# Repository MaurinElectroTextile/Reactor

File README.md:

# Tricot Reactor

### Musicals clothing made out of stretch knitted fabric sensor

S’habiller avec des vêtements technologiques c’est stylé! c’est un jeu comme le cosplay, une manière d’incarner son temps dans la mixité des influences passées, présentes et futures. Les vêtements interactifs et musicaux que nous imaginons pourraient s’inscrire dans une démarche artistique et performative mais nous avons décidé de nous adresser à un public plus large. Augmenté d'un "parfum sonore" le tricot Reacor est une sorte de vetement instrument. Rendu réactif grâce à l’intégration d’une petite carte électronique, le tricot Reactor permet d’imaginer une multitude de modèles de vêtements instruments. Tricoté à la main à partir de fils de laine et de fils conducteurs, la maille permet ainsi de capter l’élongation, la tension du tissu ainsi que les plis et contacts de la matière pour déclencher ou contrôler des sons. Une attention particulière est portée à l’intégration de l'électronique qui disparaît totalement au profit d’une esthétique simple. Intergénérationnel, ce projet est aussi un prétexte pour organiser des ateliers avec des grand mères branchées qui pourront remettre leur tricot au goût du jour.

## Scénarios

### Suivi de partition
A chaque fois que l’on bouge, presse ou plie le tricot, on "avance" d’une note dans une mélodie. Le rythme de cette mélodie correspond ainsi au rythme du mouvement de celui ou celle qui porte le vêtement et la composition fonctionne en boucle.

### Aléatoire contrôlé
Nous choisissons ici de distinguer plusieurs typologies de mouvement calme, en marche, excité, etc. Chacune de ces typologies est déterminée par la fréquence des mouvements captés. Plus on s’excite, plus les sons déclenchés sont aigus et distordus, à l’inverse, plus on est calme et plus les sons se réduisent à une sonorité simple.

### Le son extensible
Le stress exercé sur le tricot est générateur d’un son qui varie en relation directe avec l’étirement de la matière, plus le tricot est tendu plus le son est aigu. L’onde sonore est générée par synthèse. Une carte électronique dédiée permet de programmer plusieurs types de sons qui se rapprochent des sons 8-bit. Cette orientation fera l’objet d’une mise au point ultérieure car vous avons souhaité privilégier dans un premier temps une solution qui utilise des samples.

### Le son polyphonique
Dans ce dernier scénario le son sera généré par un téléphone portable assisté d’un mini système son. Ce téléphone sera aussi équipé d’une application musicale contrôlée par le vêtement. Pour réaliser un premier prototype nous avons choisi de travailler avec le système Android et donc d’aborder le développement d’une application en Java...

## Electronic
Pull on the knit cause resistor drop down. A voltage divider circuit is used to convert resistor variation into voltage value (Vs). This is done by adding a single 10K resistor (R2). To reduce power consumption of the voltage divider, the circuit is supplied (VCC) with a digital IO pin that allow on/off switching.The sketch is also implementing sleep mode.

The first prototype was using an ATTiny85 and a SOMO-4D (embedded audio-sound module) to build a small stand alone audio player. [This tutoriel explain how to program ATTiny with Arduino](http://hlt.media.mit.edu/?p=1229)

## TODO
- Translate the text in english
- Replace the SOMO with the [Teensy 3.2](https://www.pjrc.com/teensy/teensy31.html)
- Add a small amplifier

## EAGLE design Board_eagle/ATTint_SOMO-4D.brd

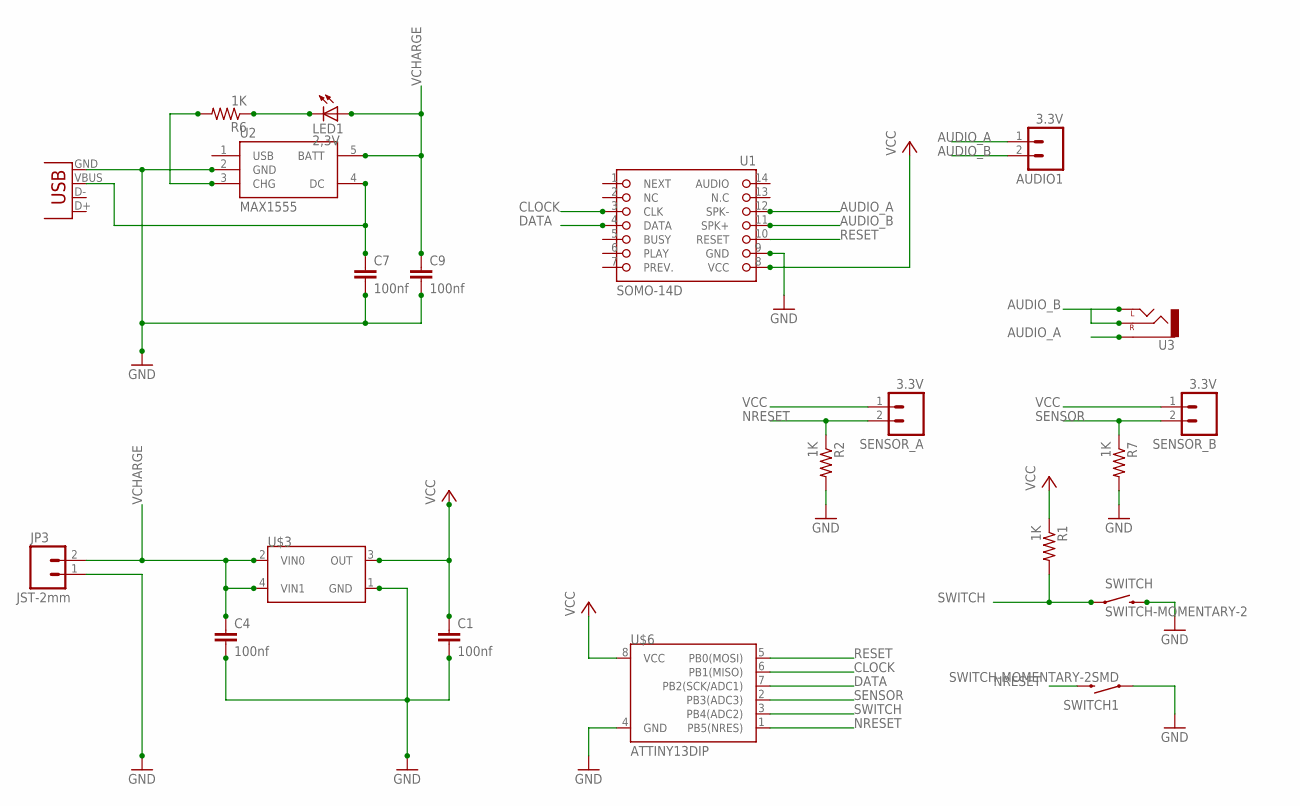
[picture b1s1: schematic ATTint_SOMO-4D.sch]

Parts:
AUDIO1: 3.3V; 1X02_LOCK_LONGPADS
C1, C4, C7, C9: 100nf; 0805
JP3: JST-2mm; JST-2-SMD
LED1: 2,3V; CHIP-LED0805
R1, R2, R6, R7: 1K; 0805
SENSOR_A: 3.3V; 1X02_LOCK_LONGPADS
SENSOR_B: 3.3V; 1X02_LOCK_LONGPADS
SWITCH: SWITCH-MOMENTARY-2; TACTILE_SWITCH_TALL
SWITCH1: SWITCH-MOMENTARY-2SMD; TACTILE_SWITCH_SMD
U1: SOMO-14D
U2: MAX1555; SOT23-5
U3: AUDIO-JACKSMD2; AUDIO-JACK-3.5MM-SMD
U$3: MCP1703; SOT-89
U$6: ATTINY13DIP; DIP08
X3: USB-SMD-NS; USB-MINIB-NOSTOP

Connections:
AUDIO_A: AUDIO1.1, U1.12 (SPK-), U3.SLEEVE
AUDIO_B: AUDIO1.2, U1.11 (SPK+), U3.RING (RIGHT), U3.TIP (LEFT)
CLOCK: U1.3 (CLK), U$6.6 (PB1(MISO))
DATA: U1.4 (DATA), U$6.7 (PB2(SCK/ADC1))
GND: C1.2, C4.2, C7.2, C9.2, JP3.1, R2.2, R7.2, SWITCH.B2 (2), SWITCH1.1, U1.9 (GND), U2.2 (GND), U$3.1 (GND), U$6.4 (GND), X3.GND
unnamed: C7.1, U2.4 (DC), X3.VBUS
unnamed: R6.2, U2.3 (CHG)
unnamed: LED1.C, R6.1
NRESET: R2.1, SENSOR_A.2, SWITCH1.3 (2), U$6.1 (PB5(NRES))
RESET: U1.10 (RESET), U$6.5 (PB0(MOSI))
SENSOR: R7.1, SENSOR_B.2, U$6.2 (PB3(ADC3))
SWITCH: R1.2, SWITCH.A2 (1), U$6.3 (PB4(ADC2))
VCC: C1.1, R1.1, SENSOR_A.1, SENSOR_B.1, U1.8 (VCC), U$3.3 (OUT), U$6.8 (VCC)
VCHARGE: C4.1, C9.1, JP3.2, LED1.A, U2.5 (BATT), U$3.2 (VIN0), U$3.4 (VIN1)

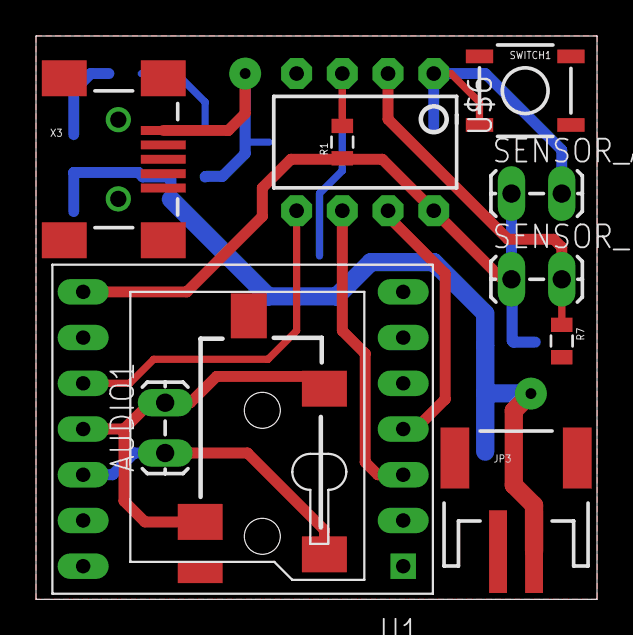
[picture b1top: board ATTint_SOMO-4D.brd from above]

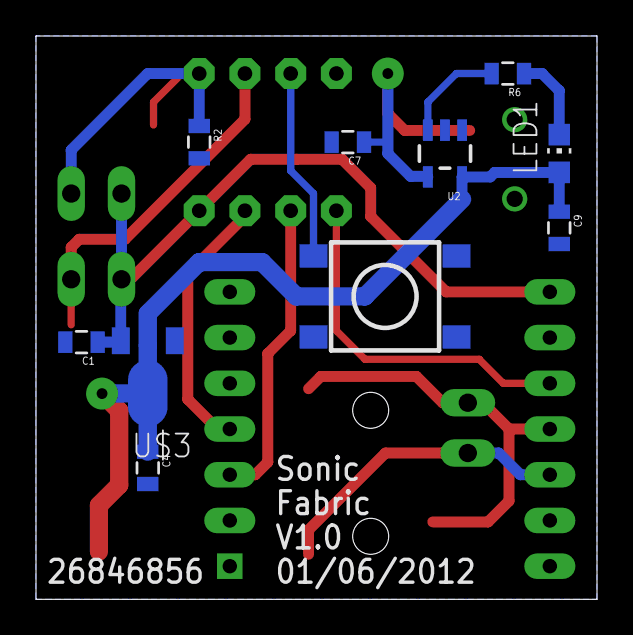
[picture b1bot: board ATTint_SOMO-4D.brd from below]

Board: 2 copper layers, 31.2 x 31.3 mm, 21 parts (10 on the bottom side), 14 nets.

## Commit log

2012-05-28 Arduino ATTiny
    sleep mode implemented
2012-05-28 Sub directory
    Added sub directory
2012-05-31 README
    add pin mapping for SOMO-4D and ATTiny85
2012-06-04 Code cleaning
2012-06-10 optimised sleeping consumption
2016-10-13 clean up
2016-10-22 added REEDME
2016-10-22 added Te
2016-10-22 Starting the V2
2016-10-22 Updated text
2016-10-22 Added Video

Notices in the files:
parts and their libraries:
SparkFun: Licensing: CC v3.0 Share-Alike You are welcome to use this library for commercial purposes.
